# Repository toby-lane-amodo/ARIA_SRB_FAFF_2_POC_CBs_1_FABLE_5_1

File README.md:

# ARIA_SRB_FAFF_2_POC_CBs_1

Electronics for **FAFF 2** — a linear actuator with force feedback, built as an OEM-style
module for soft-material characterisation. `CBs_1` is the proof-of-concept control board.

A BLDC turns a 5 mm/rev ball screw. A load cell between the screw and an interchangeable probe
tip measures applied force; a magnetic linear encoder measures displacement directly. An
STM32H723 closes a force or displacement control loop and streams force and position to a host
over USB at up to 4800 SPS.

Two build variants, differing only in maximum force: **V50N** (± 50 N) and **V10N** (± 10 N).

> **This board is deliberately larger than the final product.** It is a development-board-style
> build that precedes miniaturisation, so that every block can be brought up and measured
> independently. See [`docs/TEST_PLAN.md`](docs/TEST_PLAN.md).

## Status

**Schematic complete and integrated**, first review pass applied. All nine blocks are drawn,
the root sheet is wired, and the design is internally consistent: 398 components, 251 nets,
101 sheet pins, **0 ERC errors and 0 warnings** at `--severity-all` with nothing suppressed.
Every component has a footprint that resolves.

Review the KiCad files themselves — there is no PDF and none is generated (`DEC-0028`).
The open points to be ruled on are in
[`hardware/kicad/faff2_cbs1/SCHEMATIC_REVIEW_LOG.md`](hardware/kicad/faff2_cbs1/SCHEMATIC_REVIEW_LOG.md),
round 1. **PCB layout is the next wave**; no board file exists yet.

## Repository map

```
README.md                        this file
AGENTS.md                        conventions every session needs
docs/
  REQUIREMENTS.md                numbered requirements, traceable to the spec, both variants
  ARCHITECTURE.md                block architecture, MCU resource allocation, open gaps
  DECISIONS.md                   every judgement call, dated, with reasoning
  TEST_PLAN.md                   test points, isolation, current breaks, bring-up order
  FAFF-2-Electronics-Full.svg    THE block diagram (authoritative architecture)
  HardwareDesignStandard_DRAFT/  captain's in-house EEE design standard (verbatim draft)
  decisions/                     one record per schematic task, incl. actuator-sch-integrate.md
  review/                        the schematic review pack PDF (regenerate, never hand-edit)
hardware/
  kicad/faff2_cbs1/              the KiCad 9 project - see below
  cubemx/                        the STM32CubeMX .ioc - THE MCU pin-map authority
tools/                           re-runnable generators for the root sheet and the DRV8323S land
datasheets/                      collected datasheets (see its README for the shopping list)
```

## The KiCad project

`hardware/kicad/faff2_cbs1/faff2_cbs1.kicad_pro` — **KiCad 9 only** (DEC-0017).

| Sheet | Block |
|---|---|
| `faff2_cbs1.kicad_sch` | root - the block map, wired: 101 sheet pins (DEC-0022) |
| `power_entry_24v.kicad_sch` | 24 V in on KPJX-4S, protection |
| `power_rails.kicad_sch` | 24 V → 5 V / 3V3 / analog rails |
| `mcu.kicad_sch` | STM32H723VET6, USB3320 ULPI PHY, USB-C, QSPI RAM |
| `motor_drive.kicad_sch` | DRV8323 + FETs, current sense, motor + encoder connectors |
| `loadcell_afe.kicad_sch` | ADS1235 bridge ADC, 5 V excitation |
| `linear_encoder.kicad_sch` | RS-422 receiver, Bogen IKP11 header |
| `temp_sense.kicad_sch` | ADS1120, two RTD/NTC probe channels |
| `nvm_calibration.kicad_sch` | I2C EEPROM for calibration data |
| `ui_io.kicad_sch` | buttons, LEDs, SMA SYNC out, limit switches |

The `mcu` sheet is **A2**; every other sheet is A3. There is no `test_debug` sheet — test
coverage lives on the circuit page it covers, so the SWD + USART3 debug header, the rail probe
header and the GND hooks are blocks H, J and K on `mcu`
([`docs/decisions/actuator-rev-testdebug.md`](docs/decisions/actuator-rev-testdebug.md)).

**One block per file, one owner per file.** See `AGENTS.md`.

### Setting up the Amodo library (required before opening the project)

The project's `sym-lib-table` and `fp-lib-table` reference the house library through path
variables. Set **both**, in KiCad → *Preferences* → *Configure Paths*:

| Variable | Windows (captain's KiCad) | WSL / Linux |
|---|---|---|
| `AMODO_KICAD_LIB` | `C:\Amodo\AmodoKiCadLib` | `/mnt/c/Amodo/AmodoKiCadLib` |
| `AMODO_3D` | `C:\Amodo\AmodoKiCadLib\3D` | `/mnt/c/Amodo/AmodoKiCadLib/3D` |

`AMODO_3D` is needed separately because the Amodo footprints already reference their 3D models
through it. Without these the symbols and footprints will not resolve. See DEC-0015.

### Checking the schematic

```sh
AMODO_KICAD_LIB=/mnt/c/Amodo/AmodoKiCadLib \
  kicad-cli sch erc --severity-all --exit-code-violations \
  -o /tmp/erc.rpt hardware/kicad/faff2_cbs1/faff2_cbs1.kicad_sch
```

Currently **0 errors, 0 warnings**, with no severity suppressed (DEC-0021). Keep it that way.

## Source documents

The project document store lives in Notion, at
**TERN - University of Cambridge / ARIA_SRB_FAFF_2 / ARIA_SRB_FAFF_2 Document Store**:

| Document | Role |
|---|---|
| *Project Specification Document* | **The requirements authority.** `docs/REQUIREMENTS.md` consolidates it; where they disagree, Notion wins |
| *ARIA_SRB_FAFF_2_CBs_1 Design Log* | Electronics decisions and part selection rationale |
| *ARIA_SRB_FAFF_2_CBs_1 Block Diagram* | Excalidraw source of `docs/FAFF-2-Electronics-Full.svg` |
| *ARIA_SRB_FAFF_2 Handover Document* | Project handover |
| Specification Design Log | How the spec numbers were derived |

Also referenced: the Google Sheet **FAFF 2 EEE Prelim Calc** (force/noise budget, BLDC sizing,
power budget) and **FAFF2 Plan and Budget** (work-package phasing).

## Key parts

STM32H723VET6 · DRV8323 gate driver · USB3320 ULPI PHY · TI ADS1235 bridge ADC · TI ADS1120
temperature ADC · HBK S2M load cell (10 N / 50 N) · Bogen IKP11 magnetic linear encoder ·
KPJX-4S power connector. BLDC deliberately not fixed (DEC-0004).

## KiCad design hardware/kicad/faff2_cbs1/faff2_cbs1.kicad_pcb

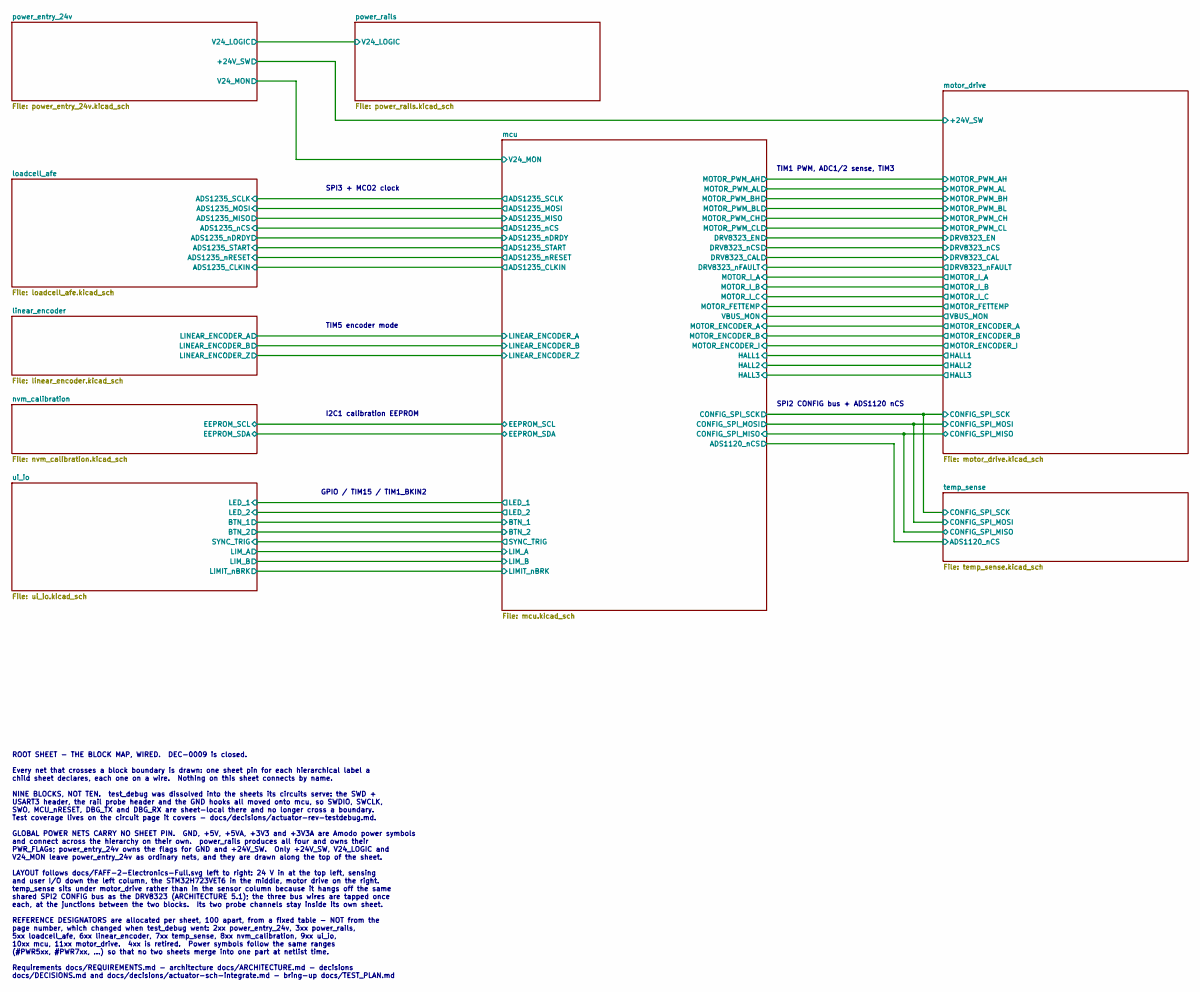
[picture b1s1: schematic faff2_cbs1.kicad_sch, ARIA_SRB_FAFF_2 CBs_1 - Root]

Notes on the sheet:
ROOT SHEET - THE BLOCK MAP, WIRED. DEC-0009 is closed. Every net that crosses a block boundary is drawn: one sheet pin for each hierarchical label a child sheet declares, each one on a wire. Nothing on this sheet connects by name. NINE BLOCKS, NOT TEN. test_debug was dissolved into the sheets its c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
GPIO / TIM15 / TIM1_BKIN2
SPI3 + MCO2 clock
TIM5 encoder mode
SPI2 CONFIG bus + ADS1120 nCS
TIM1 PWM, ADC1/2 sense, TIM3
I2C1 calibration EEPROM

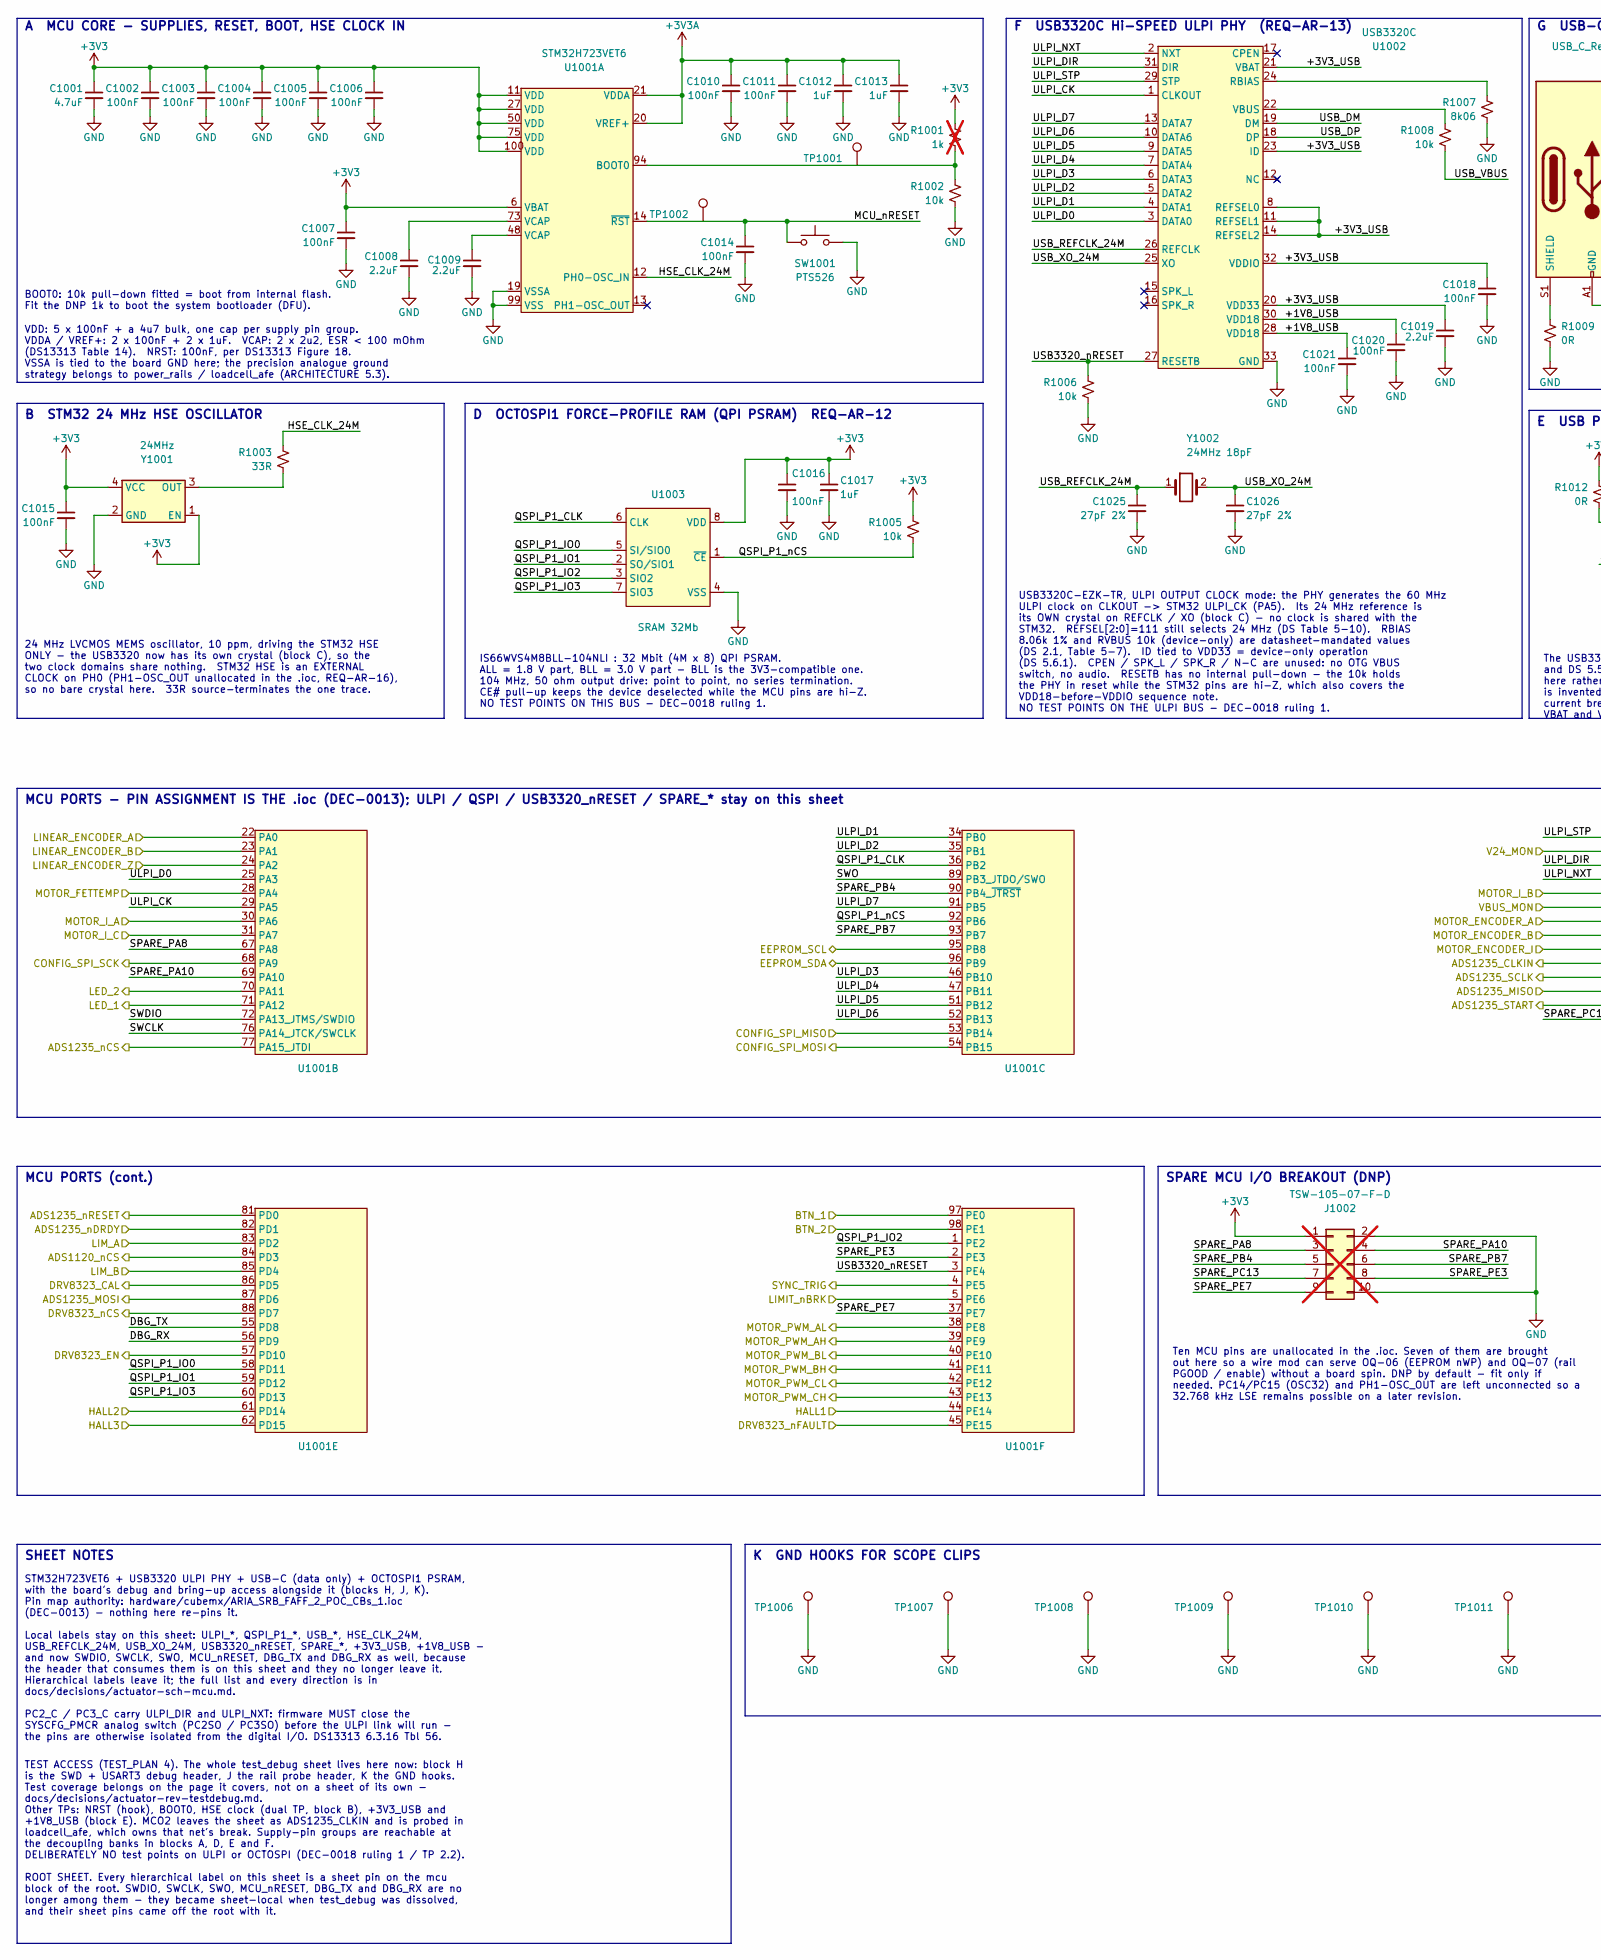
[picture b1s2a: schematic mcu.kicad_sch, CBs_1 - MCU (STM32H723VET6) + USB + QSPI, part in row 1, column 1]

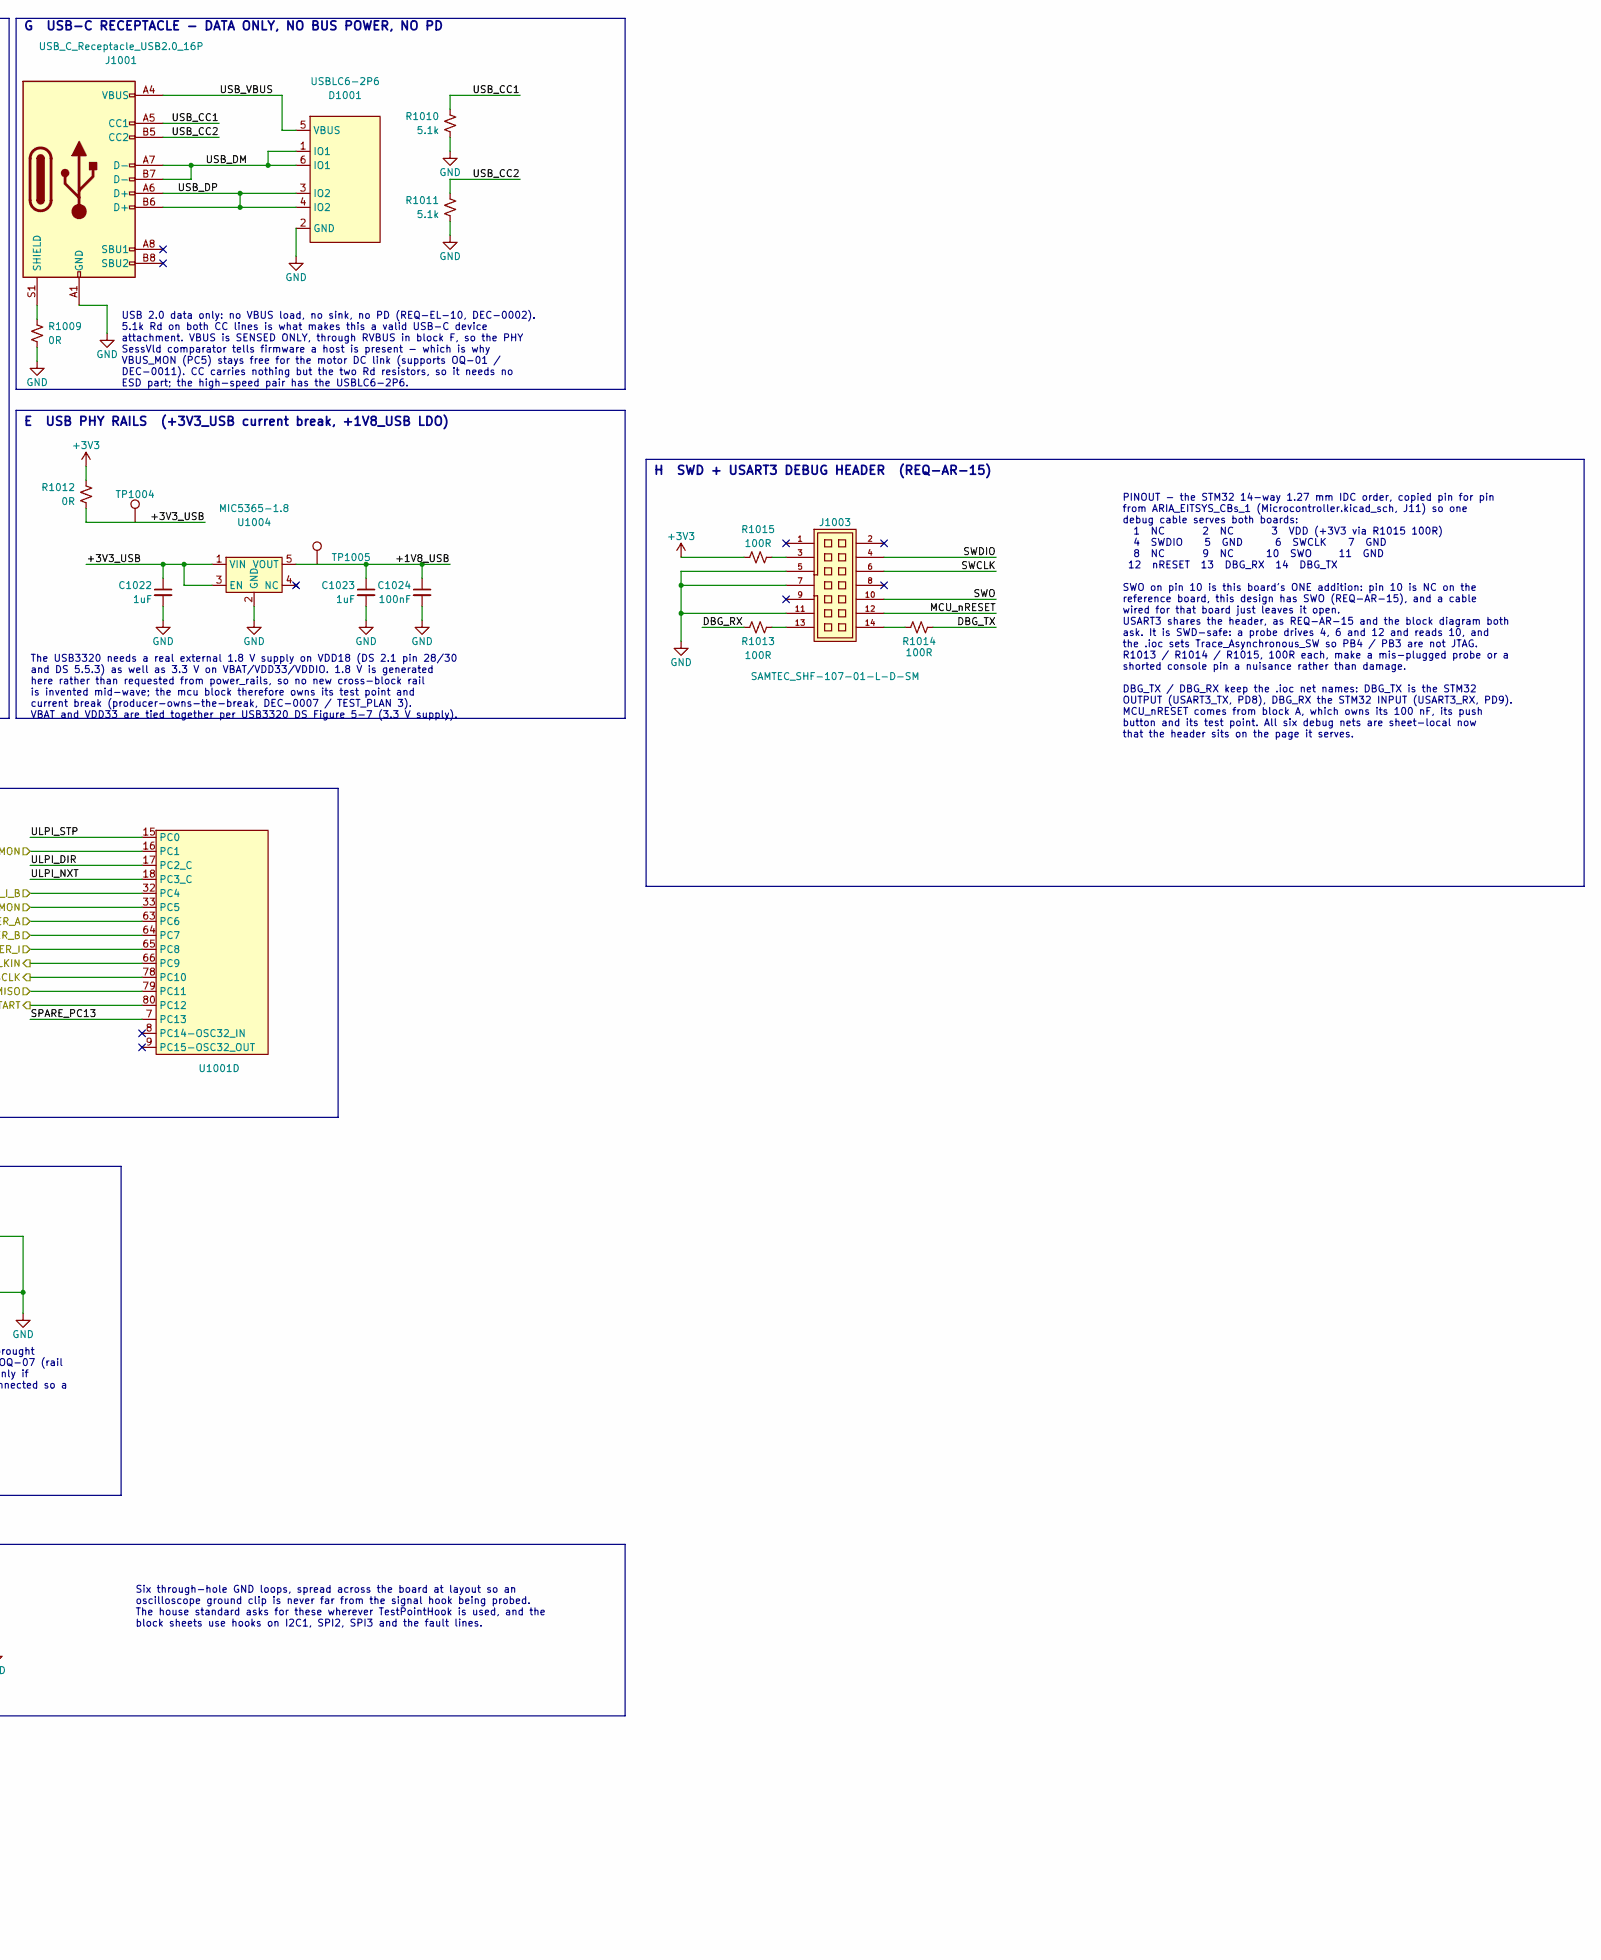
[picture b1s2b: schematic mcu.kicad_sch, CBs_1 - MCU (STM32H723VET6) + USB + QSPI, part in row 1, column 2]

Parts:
C1001: 4.7uF; C_0603_1608Metric; mpn ZRB18AR6YA475ME05L
C1002, C1003, C1004, C1005, C1006, C1007, C1010, C1011, C1014, C1015, C1016, C1018, C1020, C1021, C1024: 100nF; C_0402_1005Metric; mpn 04025C104KAT2A
C1008, C1009, C1019: 2.2uF; C_0603_1608Metric; mpn GRM188Z71C225KE43J
C1012, C1013, C1017, C1022, C1023: 1uF; C_0402_1005Metric; mpn KGM05AR51E105KH
C1025, C1026: 27pF 2%; C_0603_1608Metric; mpn 06035A270GAT2A
D1001: USBLC6-2P6; SOT666 - ST; mpn USBLC6-2P6
J1001: USB_C_Receptacle_USB2.0_16P; USB_C_Receptacle_GCT_USB4110; mpn USB4110-GF-A
J1002: TSW-105-07-F-D; mpn TSW-105-07-F-D; not fitted
J1003: SAMTEC_SHF-107-01-L-D-SM; mpn SHF-107-01-L-D-SM
R1001: 1k; R_0603_1608Metric; mpn CR0603AFX-1001ELF; not fitted
R1002, R1005, R1006, R1008: 10k; R_0603_1608Metric; mpn ERJ-3EKF1002V
R1003: 33R; R_0603_1608Metric; mpn ERJ-3EKF33R0V
R1007: 8k06; R_0603_1608Metric; mpn CRCW06038K06FKEA
R1009, R1012: 0R; R_0603_1608Metric; mpn RC0603FR-070RL
R1010, R1011: 5.1k; R_0603_1608Metric; mpn CRCW06035K10FKEBC
R1013, R1014, R1015: 100R; R_0603_1608Metric; mpn ERJ-3EKF1000V
SW1001: PTS526; PTS526_1.5mm_G; mpn PTS526 SK15 SMTR2 LFS
TP1001: BOOT0; TestPoint_Pad_D1.0mm
TP1002: nRST; KeystoneMiniatureTestLoop; mpn 5002
TP1004: 3V3U; TestPoint_Pad_D1.0mm
TP1005: 1V8U; TestPoint_Pad_D1.0mm
TP1006, TP1007, TP1008, TP1009, TP1010, TP1011: GND; KeystoneMiniatureTestLoop; mpn 5002
U1001: STM32H723VET6; LQFP100; mpn STM32H723VET6
U1002: USB3320C; QFN-32 - 5x5mm - P0.5mm - EP3.3x3.3mm; mpn USB3320C-EZK-TR
U1003: SRAM 32Mb; SOIC-8 5x4; mpn IS66WVS4M8BLL-104NLI
U1004: MIC5365-1.8; SC-70-5; mpn MIC5365-1.8YC5-TR
Y1001: 24MHz; OSC_3.2MMX2.5MM; mpn ASEMB-24.000MHZ-LY-T
Y1002: 24MHz 18pF; Crystal_SMD_0603_2Pin_6.0x3.5mm; mpn ECS-240-12-23G-JGN-TR

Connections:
+3V3: C1001.1, C1002.1, C1003.1, C1004.1, C1005.1, C1006.1, C1007.1, C1015.1, C1016.1, C1017.1, J1002.1, R1001.1, R1005.1, R1012.1, R1015.1, U1001.6 (VBAT), U1001.11 (VDD), U1001.27 (VDD), U1001.50 (VDD), U1001.75 (VDD), U1001.100 (VDD), U1003.8 (VDD), Y1001.1 (EN), Y1001.4 (VCC); also elsewhere on the board
+3V3A: C1010.1, C1011.1, C1012.1, C1013.1, U1001.20 (VREF+), U1001.21 (VDDA); also elsewhere on the board
/linear_encoder/LINEAR_ENCODER_A: U1001.22 (PA0); also elsewhere on the board
/linear_encoder/LINEAR_ENCODER_B: U1001.23 (PA1); also elsewhere on the board
/linear_encoder/LINEAR_ENCODER_Z: U1001.24 (PA2); also elsewhere on the board
/loadcell_afe/ADS1235_CLKIN: U1001.66 (PC9); also elsewhere on the board
/loadcell_afe/ADS1235_MISO: U1001.79 (PC11); also elsewhere on the board
/loadcell_afe/ADS1235_MOSI: U1001.87 (PD6); also elsewhere on the board
/loadcell_afe/ADS1235_SCLK: U1001.78 (PC10); also elsewhere on the board
/loadcell_afe/ADS1235_START: U1001.80 (PC12); also elsewhere on the board
/loadcell_afe/ADS1235_nCS: U1001.77 (PA15_JTDI); also elsewhere on the board
/loadcell_afe/ADS1235_nDRDY: U1001.82 (PD1); also elsewhere on the board
/loadcell_afe/ADS1235_nRESET: U1001.81 (PD0); also elsewhere on the board
/mcu/+1V8_USB: C1020.1, C1021.1, C1023.1, C1024.1, TP1005.1, U1002.28 (VDD18), U1002.30 (VDD18), U1004.5 (VOUT)
/mcu/+3V3_USB: C1018.1, C1019.1, C1022.1, R1012.2, TP1004.1, U1002.8 (REFSEL0), U1002.11 (REFSEL1), U1002.14 (REFSEL2), U1002.20 (VDD33), U1002.21 (VBAT), U1002.23 (ID), U1002.32 (VDDIO), U1004.1 (VIN), U1004.3 (EN)
/mcu/BTN_1: U1001.97 (PE0); also elsewhere on the board
/mcu/BTN_2: U1001.98 (PE1); also elsewhere on the board
/mcu/DBG_RX: R1013.1, U1001.56 (PD9)
/mcu/DBG_TX: R1014.2, U1001.55 (PD8)
/mcu/DRV8323_CAL: U1001.86 (PD5); also elsewhere on the board
/mcu/DRV8323_EN: U1001.57 (PD10); also elsewhere on the board
/mcu/DRV8323_nCS: U1001.88 (PD7); also elsewhere on the board
/mcu/DRV8323_nFAULT: U1001.45 (PE15); also elsewhere on the board
/mcu/EEPROM_SCL: U1001.95 (PB8); also elsewhere on the board
/mcu/EEPROM_SDA: U1001.96 (PB9); also elsewhere on the board
/mcu/HALL1: U1001.44 (PE14); also elsewhere on the board
/mcu/HALL2: U1001.61 (PD14); also elsewhere on the board
/mcu/HALL3: U1001.62 (PD15); also elsewhere on the board
/mcu/HSE_CLK_24M: R1003.1, U1001.12 (PH0-OSC_IN)
/mcu/LED_1: U1001.71 (PA12); also elsewhere on the board
/mcu/LED_2: U1001.70 (PA11); also elsewhere on the board
/mcu/LIMIT_nBRK: U1001.5 (PE6); also elsewhere on the board
/mcu/LIM_A: U1001.83 (PD2); also elsewhere on the board
/mcu/LIM_B: U1001.85 (PD4); also elsewhere on the board
/mcu/MCU_nRESET: C1014.1, J1003.12, SW1001.1_2, TP1002.1, U1001.14 (~RST)
/mcu/MOTOR_ENCODER_A: U1001.63 (PC6); also elsewhere on the board
/mcu/MOTOR_ENCODER_B: U1001.64 (PC7); also elsewhere on the board
/mcu/MOTOR_ENCODER_I: U1001.65 (PC8); also elsewhere on the board
/mcu/MOTOR_FETTEMP: U1001.28 (PA4); also elsewhere on the board
/mcu/MOTOR_I_A: U1001.30 (PA6); also elsewhere on the board
/mcu/MOTOR_I_B: U1001.32 (PC4); also elsewhere on the board
/mcu/MOTOR_I_C: U1001.31 (PA7); also elsewhere on the board
/mcu/MOTOR_PWM_AH: U1001.39 (PE9); also elsewhere on the board
/mcu/MOTOR_PWM_AL: U1001.38 (PE8); also elsewhere on the board
/mcu/MOTOR_PWM_BH: U1001.41 (PE11); also elsewhere on the board
/mcu/MOTOR_PWM_BL: U1001.40 (PE10); also elsewhere on the board
/mcu/MOTOR_PWM_CH: U1001.43 (PE13); also elsewhere on the board
/mcu/MOTOR_PWM_CL: U1001.42 (PE12); also elsewhere on the board
/mcu/QSPI_P1_CLK: U1001.36 (PB2), U1003.6 (CLK)
/mcu/QSPI_P1_IO0: U1001.58 (PD11), U1003.5 (SI/SIO0)
/mcu/QSPI_P1_IO1: U1001.59 (PD12), U1003.2 (SO/SIO1)
/mcu/QSPI_P1_IO2: U1001.1 (PE2), U1003.3 (SIO2)
/mcu/QSPI_P1_IO3: U1001.60 (PD13), U1003.7 (SIO3)
/mcu/QSPI_P1_nCS: R1005.2, U1001.92 (PB6), U1003.1 (~CE)
/mcu/SPARE_PA8: J1002.3, U1001.67 (PA8)
/mcu/SPARE_PA10: J1002.4, U1001.69 (PA10)
/mcu/SPARE_PB4: J1002.5, U1001.90 (PB4_~JTRST)
/mcu/SPARE_PB7: J1002.6, U1001.93 (PB7)
/mcu/SPARE_PC13: J1002.7, U1001.7 (PC13)
/mcu/SPARE_PE3: J1002.8, U1001.2 (PE3)
/mcu/SPARE_PE7: J1002.9, U1001.37 (PE7)
/mcu/SWCLK: J1003.6, U1001.76 (PA14_JTCK/SWCLK)
/mcu/SWDIO: J1003.4, U1001.72 (PA13_JTMS/SWDIO)
/mcu/SWO: J1003.10, U1001.89 (PB3_JTDO/SWO)
/mcu/SYNC_TRIG: U1001.4 (PE5); also elsewhere on the board
/mcu/ULPI_CK: U1001.29 (PA5), U1002.1 (CLKOUT)
/mcu/ULPI_D0: U1001.25 (PA3), U1002.3 (DATA0)
/mcu/ULPI_D1: U1001.34 (PB0), U1002.4 (DATA1)
/mcu/ULPI_D2: U1001.35 (PB1), U1002.5 (DATA2)
/mcu/ULPI_D3: U1001.46 (PB10), U1002.6 (DATA3)
/mcu/ULPI_D4: U1001.47 (PB11), U1002.7 (DATA4)
/mcu/ULPI_D5: U1001.51 (PB12), U1002.9 (DATA5)
/mcu/ULPI_D6: U1001.52 (PB13), U1002.10 (DATA6)
/mcu/ULPI_D7: U1001.91 (PB5), U1002.13 (DATA7)
/mcu/ULPI_DIR: U1001.17 (PC2_C), U1002.31 (DIR)
/mcu/ULPI_NXT: U1001.18 (PC3_C), U1002.2 (NXT)
/mcu/ULPI_STP: U1001.15 (PC0), U1002.29 (STP)
/mcu/USB3320_nRESET: R1006.1, U1001.3 (PE4), U1002.27 (RESETB)
/mcu/USB_CC1: J1001.A5 (CC1), R1010.1
/mcu/USB_CC2: J1001.B5 (CC2), R1011.1
/mcu/USB_DM: D1001.1 (IO1), D1001.6 (IO1), J1001.A7 (D-), J1001.B7 (D-), U1002.19 (DM)
/mcu/USB_DP: D1001.3 (IO2), D1001.4 (IO2), J1001.A6 (D+), J1001.B6 (D+), U1002.18 (DP)
/mcu/USB_REFCLK_24M: C1025.1, U1002.26 (REFCLK), Y1002.1
/mcu/USB_VBUS: D1001.5 (VBUS), J1001.A4 (VBUS), J1001.A9 (VBUS), J1001.B4 (VBUS), J1001.B9 (VBUS), R1008.2
/mcu/USB_XO_24M: C1026.1, U1002.25 (XO), Y1002.2
/mcu/V24_MON: U1001.16 (PC1); also elsewhere on the board
/mcu/VBUS_MON: U1001.33 (PC5); also elsewhere on the board
/temp_sense/ADS1120_nCS: U1001.84 (PD3); also elsewhere on the board
/temp_sense/CONFIG_SPI_MISO: U1001.53 (PB14); also elsewhere on the board
/temp_sense/CONFIG_SPI_MOSI: U1001.54 (PB15); also elsewhere on the board
/temp_sense/CONFIG_SPI_SCK: U1001.68 (PA9); also elsewhere on the board
GND: C1001.2, C1002.2, C1003.2, C1004.2, C1005.2, C1006.2, C1007.2, C1008.2, C1009.2, C1010.2, C1011.2, C1012.2, C1013.2, C1014.2, C1015.2, C1016.2, C1017.2, C1018.2, C1019.2, C1020.2, C1021.2, C1022.2, C1023.2, C1024.2, C1025.2, C1026.2, D1001.2 (GND), J1001.A1 (GND), J1001.A12 (GND), J1001.B1 (GND), J1001.B12 (GND), J1002.2, J1002.10, J1003.5, J1003.7, J1003.11, R1002.2, R1006.2, R1007.2, R1009.2, R1010.2, R1011.2, SW1001.3_4, TP1006.1, TP1007.1, TP1008.1, TP1009.1, TP1010.1, TP1011.1, U1001.10 (VSS), U1001.19 (VSSA), U1001.26 (VSS), U1001.49 (VSS), U1001.74 (VSS), U1001.99 (VSS), U1002.33 (GND), U1003.4 (VSS), U1004.2 (GND), Y1001.2 (GND); also elsewhere on the board
unnamed: C1008.1, U1001.73 (VCAP)
unnamed: C1009.1, U1001.48 (VCAP)
unnamed: J1001.S1 (SHIELD), R1009.1
unnamed: J1003.3, R1015.2
unnamed: J1003.13, R1013.2
unnamed: J1003.14, R1014.1
unnamed: R1001.2, R1002.1, TP1001.1, U1001.94 (BOOT0)
unnamed: R1007.1, U1002.24 (RBIAS)
unnamed: R1008.1, U1002.22 (VBUS)
unnamed: R1003.2, Y1001.3 (OUT)

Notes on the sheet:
BOOT0: 10k pull-down fitted = boot from internal flash. Fit the DNP 1k to boot the system bootloader (DFU).
MCU PORTS (cont.)
SPARE MCU I/O BREAKOUT (DNP)
IS66WVS4M8BLL-104NLI : 32 Mbit (4M x 8) QPI PSRAM. ALL = 1.8 V part, BLL = 3.0 V part - BLL is the 3V3-compatible one. 104 MHz, 50 ohm output drive: point to point, no series termination. CE# pull-up keeps the device deselected while the MCU pins are hi-Z. NO TEST POINTS ON THIS BUS - DEC-0018 ruli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
A MCU CORE - SUPPLIES, RESET, BOOT, HSE CLOCK IN
USB3320C-EZK-TR, ULPI OUTPUT CLOCK mode: the PHY generates the 60 MHz ULPI clock on CLKOUT -> STM32 ULPI_CK (PA5). Its 24 MHz reference is its OWN crystal on REFCLK / XO (block C) - no clock is shared with the STM32. REFSEL[2:0]=111 still selects 24 MHz (DS Table 5-10). RBIAS 8.06k 1% and RVBUS 10k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
F USB3320C Hi-SPEED ULPI PHY (REQ-AR-13)
D OCTOSPI1 FORCE-PROFILE RAM (QPI PSRAM) REQ-AR-12
The USB3320 needs a real external 1.8 V supply on VDD18 (DS 2.1 pin 28/30 and DS 5.5.3) as well as 3.3 V on VBAT/VDD33/VDDIO. 1.8 V is generated here rather than requested from power_rails, so no new cross-block rail is invented mid-wave; the mcu block therefore owns its test point and current brea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
SHEET NOTES
B STM32 24 MHz HSE OSCILLATOR
K GND HOOKS FOR SCOPE CLIPS
E USB PHY RAILS (+3V3_USB current break, +1V8_USB LDO)
Six through-hole GND loops, spread across the board at layout so an oscilloscope ground clip is never far from the signal hook being probed. The house standard asks for these wherever TestPointHook is used, and the block sheets use hooks on I2C1, SPI2, SPI3 and the fault lines.
PINOUT - the STM32 14-way 1.27 mm IDC order, copied pin for pin from ARIA_EITSYS_CBs_1 (Microcontroller.kicad_sch, J11) so one debug cable serves both boards: 1 NC 2 NC 3 VDD (+3V3 via R1015 100R) 4 SWDIO 5 GND 6 SWCLK 7 GND 8 NC 9 NC 10 SWO 11 GND 12 nRESET 13 DBG_RX 14 DBG_TX SWO on pin 10 is thi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
H SWD + USART3 DEBUG HEADER (REQ-AR-15)
TEST ACCESS (TEST_PLAN 4). The whole test_debug sheet lives here now: block H is the SWD + USART3 debug header, J the rail probe header, K the GND hooks. Test coverage belongs on the page it covers, not on a sheet of its own - docs/decisions/actuator-rev-testdebug.md. Other TPs: NRST (hook), BOOT0,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
STM32H723VET6 + USB3320 ULPI PHY + USB-C (data only) + OCTOSPI1 PSRAM, with the board's debug and bring-up access alongside it (blocks H, J, K). Pin map authority: hardware/cubemx/ARIA_SRB_FAFF_2_POC_CBs_1.ioc (DEC-0013) - nothing here re-pins it. Local labels stay on this sheet: ULPI_*, QSPI_P1_*,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
VDD: 5 x 100nF + a 4u7 bulk, one cap per supply pin group. VDDA / VREF+: 2 x 100nF + 2 x 1uF. VCAP: 2 x 2u2, ESR < 100 mOhm (DS13313 Table 14). NRST: 100nF, per DS13313 Figure 18. VSSA is tied to the board GND here; the precision analogue ground strategy belongs to power_rails / loadcell_afe (ARCHI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
USB 2.0 data only: no VBUS load, no sink, no PD (REQ-EL-10, DEC-0002). 5.1k Rd on both CC lines is what makes this a valid USB-C device attachment. VBUS is SENSED ONLY, through RVBUS in block F, so the PHY SessVld comparator tells firmware a host is present - which is why VBUS_MON (PC5) stays free 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
G USB-C RECEPTACLE - DATA ONLY, NO BUS POWER, NO PD
24 MHz LVCMOS MEMS oscillator, 10 ppm, driving the STM32 HSE ONLY - the USB3320 now has its own crystal (block C), so the two clock domains share nothing. STM32 HSE is an EXTERNAL CLOCK on PH0 (PH1-OSC_OUT unallocated in the .ioc, REQ-AR-16), so no bare crystal here. 33R source-terminates the one t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
Ten MCU pins are unallocated in the .ioc. Seven of them are brought out here so a wire mod can serve OQ-06 (EEPROM nWP) and OQ-07 (rail PGOOD / enable) without a board spin. DNP by default - fit only if needed. PC14/PC15 (OSC32) and PH1-OSC_OUT are left unconnected so a 32.768 kHz LSE remains possi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
MCU PORTS - PIN ASSIGNMENT IS THE .ioc (DEC-0013); ULPI / QSPI / USB3320_nRESET / SPARE_* stay on this sheet
